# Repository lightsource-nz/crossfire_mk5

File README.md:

# crossfire

USB-MIDI forwarding between every instrument on the host port: notes played on one instrument
reach all the others, with no computer in between.

crossfire runs on its own board, the **crossfire production board, revision 0.1** -- an RP2350
hosting four instruments through an on-board hub, powered and reached over one USB-C port, with
two indicators in place of a display. That is the default target of every script here. The same
application also runs on two development boards: a Pico 2 wearing the Pico-OLED-1.3, and the
stock RP2040 Pico, both with a small OLED status display.

## The production board, revision 0.1

Revision 0.1 went to the fabricator, assembled, in October 2026, and is the board the firmware
here runs on. Its design, and every decision behind it, is in `pcb/` (`pcb/README.md`); the files
that were submitted and a specification of the board as built are in `pcb/releases/v0.1/`. The
design files themselves have since moved on to revision 0.2.

The firmware target is `crossfire_v01`: its own pico-sdk board definition in `boards/`, its wiring
in `crates/light-board-crossfire-v01`, and the application instantiated in `module/crossfire_v01`.
Its instruments are hosted on a PIO pair to the on-board hub -- the framework's `usb-host-pio`
role, the same host stack the development boards run on their native controller -- and its USB-C
port is the device: the console rides it, as well as the debug header's UART, and so does the
1200-baud route into the bootloader, so the board is written over its own connector with no probe.
The build fixes the system clock at 240 MHz (`CROSSFIRE_V01_SYS_CLK_KHZ`; 192000 and 120000 are
the alternatives), because the PIO host wants a multiple of 12 MHz and the SDK's default is not
one. What it shares with the Pico 2 below the application -- probation, firmware
self-replacement -- is `crates/crossfire-rp2350`.

With no display, it shows its state on two indicators: green lit while an instrument is mounted
and interrupted by traffic, red lit while the supply is known to be short of what four ports could
ask for. It reads that from the receptacle's CC lines twice a second, since a worn cable's CC
contact can make and break after start-up (`power` on the console reports them on request),
releases the on-board hub once the host stack is listening and the supply's advertisement has held
for 100 ms, or after a second without one (`hub on|off` re-enumerates it or holds it), and `stats`
reports the PIO host's frame engine beside the application's own counters.

What has been shown on the board: the PIO host enumerates the hub and two USB-MIDI instruments
behind it, and notes played on them reach the board and are forwarded, with the activity indicator
following. The CC lines read all three advertisements correctly -- the USB default, 1.5 A and
3 A -- and the default and 3 A on either line, as the cable is turned over. A new image reaches it
over its console and keeps itself (below). `scripts/read-cc.ps1` reads the CC lines through the
debug header, which leaves the USB-C port free for the supply under test. Running from a USB-PD
supply, a keyboard played a synth through the board, notes and chords starting and stopping as
played, with the synth's controls reaching the keyboard the other way. `trace on` on the console
logs every message read from and written to each instrument, and `send` writes one to an instrument
directly. Measured from its ports (below), a message crosses it in 0.2 to 1.3 ms and nothing is lost
up to 16,000 messages a second. Not yet shown on hardware: the recovery of a hub port disabled for a device error, which
is tested on the host only.

## Building

This project is built against the **light framework** checkout beside it (`../light_mk5`); set
`LIGHT_PATH` for another layout. The framework supplies the C shell, the portable crates, the
ports, the asset compilers and the shared script layer. Everything that is crossfire's own --
the application, the board modules, the version, the signing key, the flash map -- is here.

```
scripts/build.ps1 [-Target crossfire_v01|crossfire_pico2|crossfire_pico]
scripts/flash.ps1                             # the production board, over its own USB-C port
scripts/update.ps1                            # the production board, while it runs (below)
scripts/console.ps1                           # its console, on the same port
scripts/flash.ps1 -Target crossfire_pico2     # a Pico, over SWD through a debug probe
scripts/debug.ps1 -Target crossfire_pico2
scripts/console.ps1 -Port <COM>               # a Pico's console rides the probe's UART
scripts/test.ps1                              # the application's host tests
```

With no `-Target`, the scripts build and write `crossfire_v01`, the production board.

CI (`.github/workflows/ci.yml`) runs the same scripts through the framework's reusable workflows:
the host tests, and a firmware build of each board -- the two RP2350 legs with their bootloader --
whose images are kept as artifacts.

## Running it without a board

```
scripts/sim.ps1 [-Release]                    # crossfire on a simulated board, in a window
```

`tools/crossfire-sim` runs the application crate -- the same one the firmware links, unchanged --
over the framework's simulated seams (`light_mk5/tools/light-sim`): an SH1107 panel that decodes
the real driver's commands onto a simulated glass, the indicator, the BOOTSEL button, a hub with
four sockets that instruments plug into and play from, and the console, in a desktop window. The
font, the look-and-feel and the interface are compiled at start-up by the same code the firmware
build runs, so the glass shows what the panel shows. Console lines can also be piped in on standard
input, and the log is echoed to standard output. What it simulates is the application's logic
against its seams, with a person at the controls; it is not a model of a chip, and the host tests
remain the place a module's behaviour is pinned down. The board it stands in for is a Pico with
the Pico-OLED-1.3; the production board's two indicators are not simulated yet.

## Images are signed

Every build signs its image and the device's flash map with `keys/dev.pem`, which is public and
protects nothing (see `keys/README.md`); a release is signed with a key that never appears here.
The flash map gives the application an A/B pair, so an update is written to the slot that is not
running and chosen on the next boot, and a data partition for the assets. What the hardware
verifies, and when, is specified in the framework's `documents/11-secure-boot-and-update.md`.

## A new image keeps itself only if it works

An update is started on probation: the RP2350's boot ROM runs it once, and unless it commits itself
the previous image boots again -- at the next reset, or when the ROM's probation watchdog runs out
some seventeen seconds after the boot. crossfire makes that decision on its own
(`crates/light_app_crossfire/src/probation.rs`). At boot the board asks the ROM whether the running
image is a candidate; if so, the application watches itself for three seconds after every module has
loaded and commits once the main loop is turning over, the console core is alive, and the display
has taken a whole frame with no bus timeout. A panic, a stopped loop or a failed check means no
commit, and so the old firmware comes back; a candidate that has not passed by ten seconds of uptime
is given up on well inside the ROM's window. The console reports every step as `probation: ...`.
The production board has no display and is not asked about one. The RP2040 has no second slot and
puts nothing on probation, so there every image is already kept.

An image reaches the other slot over the console, so a board that is running needs no BOOTSEL, no
button and no probe to be given new firmware: `scripts/update.ps1` builds the production board's
image, sends it over the board's own USB-C port a line at a time (the console commands `receive`
and `rx`), and follows the board through its reboot to say whether the new image kept itself and
which slot it is running. A 161 KiB image takes about fifteen seconds. The board has to be running
firmware that has these commands, which `scripts/flash.ps1` puts on once.

## Measuring a board

Two small boards plugged into crossfire's ports measure it the way an instrument sees it
(`crates/crossfire-bench`). The **timer**, an RP2350-Zero with a debug probe on its SWD pads, sends
numbered messages through the board. The **echo**, an RP2040-Zero, sends each one back and toggles a
wire to the timer as it arrives (GP2 to GP2, with a ground wire beside it). Nothing else should be
plugged into crossfire during a run. The timer records three things:

- latency one way, from sending a message to the echo's wire changing;
- the round trip, from sending to the echo arriving back;
- throughput, at rates from 500 to 24,000 messages a second, with every gap in the echoes counted.

```
scripts/flash.ps1 -Target crossfire_bench_echo    # once, with BOOT held as it is plugged into the computer
scripts/bench.ps1 -Flash                          # writes the timer over SWD, runs, prints the figures
scripts/bench.ps1                                 # another run
```

The echo's OUT endpoint takes sixty-four bytes. Hold its GP3 to ground at power-up to give it four
bytes instead, like an instrument that takes one event at a time. The timer's figures stay in RAM,
and the script reads them over SWD without halting anything; its log is on the UART at GP0.

What the production board measures, with the sixty-four-byte echo:

| | min | median | 99th percentile | max |
|---|---|---|---|---|
| one way | 0.22 ms | 0.74 ms | 1.23 ms | 1.26 ms |
| round trip | 1.2 ms | 1.7 ms | 2.2 ms | 2.3 ms |

Each spreads evenly over one millisecond, the USB frame: a message waits in an instrument until the
board next asks it for one, and is written to the next instrument as soon as the board has read
it. Under load it forwards every message up to 16,000 a second in each direction, the most the
timer can send and some sixteen times what a MIDI cable carries, with a round trip of 2 to 2.7 ms.
What the board cannot take is counted as `departing` in `stats`, never lost unseen. The bench
found the PIO host's two largest costs: an instrument sending each frame lost every other packet,
and every forwarded message waited a frame to be written.

## The development boards

Before the production board existed, crossfire was brought up on two Picos, and both are still
built and tested:

- **`crossfire_pico2`** -- a Pico 2 wearing the Pico-OLED-1.3. The same RP2350 as the production
  board, with the same bootloader, flash map and probation, but its instruments on the native USB
  port in its host role and an OLED status display. Flashed and debugged over SWD; its console
  rides the debug probe's UART.
- **`crossfire_pico`** -- the stock RP2040 Pico, with the same display. No second slot and no
  bootloader: its image is its whole flash. Flashed over SWD as well.

Both show their state on the display rather than on two indicators, and both need a debug probe,
which the production board does not.

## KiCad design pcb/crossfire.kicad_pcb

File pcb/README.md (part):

# crossfire hardware

The production board: an RP2350 hosting four USB instruments through a hub, with one USB-C
connector that carries both its power and its link to a computer.

**Status: the files here are revision 0.2, in design.** Revision 0.1 was ordered assembled in
October 2026 and delivered in November; it is final, and the files that went to the fabricator and
a specification of the board as built are under `releases/v0.1/`. Changes from here on are
revision 0.2's: the first, a Power Delivery sink on the upstream connector and an input rail rated
for 20 V, is in the schematic and on the board, which grew 10 mm deeper for it (under *Layout*).
Unless a section says it was measured on
revision 0.1, a number below is a budget or a datasheet figure. A predecessor design exists elsewhere as a sketch of an earlier vision; it was never
manufactured or validated, so nothing here is inherited from it — individual parts are reused only
where they stand up on their own.

**This is the reduced first design.** An earlier revision of this board carried a Power Delivery
sink on a second connector, a charger and a cell, and a radio. Those are deferred, not rejected: they
made a first board that was hard to lay out and harder to bring up, and none of them is needed to
prove the thing the product is for. That revision is kept whole in the history at commit `bb66643`.
Revision 0.2 brings the first of them back, the sink, on the one connector this board already has.

## What the board has to do

- Host four USB-MIDI instruments at once, on four type-A receptacles, each supplied from a 5 V
  rail the board makes from its input.
- Keep the firmware that already exists: the USB device role and its console, and the signed A/B
  image pair with probation.
- Present itself to a computer on the upstream connector *while* hosting the instruments, so the two
  roles live on separate interfaces.
- Take all of its power from that same upstream USB-C connector, and share out whatever the source
  there offers between the four ports and its own electronics.

## Three decisions shape everything else

### 1. Two USB roles on two interfaces

The RP2350 has **one** USB controller, and the board needs two roles at once: host for the four
instruments, device for the computer on the upstream connector. The roles are kept apart on separate
interfaces — the hardware controller takes one, and a full-speed port built in PIO takes the other.
Nothing is multiplexed and nothing switches role, so a computer and the instruments are live at the
same time.

**The hardware controller faces outward as the device, and PIO hosts the hub.** The deciding
argument is recovery, and it beats the alternative on its own terms:

- **The boot ROM drives the hardware controller.** Putting that pair on the upstream connector means
  BOOTSEL and USB DFU work on the connector the product actually has. Recovery needs no debug probe,
  no case opened, nobody on the bench.
- **It makes the risky new thing the recoverable one.** The host side is what has to be rebuilt, and
  if that goes wrong the board can still be reflashed over its own port. The other way round, a rough
  device port takes the console and DFU with it and leaves only SWD.
- **Bring-up starts working rather than blocked.** The board is programmable and has a console over
  its own connector before any of the new firmware exists, so the host side can be brought up
  incrementally against a board that already talks.

What it costs, plainly: **the host role moves onto a new transport.** The existing host stack sits
behind a host-controller seam, so the stack, the hub handling and the MIDI layer above it are kept —
but the packet-level transport underneath becomes a full-speed USB host built in PIO, which does not
exist in this tree. That is the single largest piece of new firmware this board asks for, and it is
the harder of the two roles to build: it has to generate frames, schedule transactions across four
devices and a hub, and handle retries.

The device side, by contrast, is already proven on hardware — the console rides it today. The one
addition there is the computer-facing MIDI interface, which is a device class on a working stack.

**The upstream connector is unambiguous.** It sinks power and acts as a device, both, always — so
the CC lines mean one thing, there is no role to choose, and the charger-versus-computer guess that a
multiplexed design would have needed is gone. Electrically it is also the simpler end: the hardware
controller's pins carry their own impedance matching and pull-ups, so the pair needs only an ESD
array and the receptacle's two data pairs tied together, so a cable can go in either way up.

**The PIO port sets the system clock, and it sets it upward: 240 MHz.** Full-speed bit timing off PIO
wants a system clock that is an integer multiple of 12 MHz, so the state-machine divider is exact and
the bit period carries no fractional jitter. The stock 150 MHz is not such a multiple. Going *down* to
120 MHz would satisfy it at the cost of a fifth of the loop; going up to 240 MHz satisfies it and buys
the loop instead, and four things line up on that number:

- **12 MHz × 20.** Twenty system cycles per bit, and an exact divide by two if the state machine wants
  to run at 120 MHz. Either way the divider is an integer.
- **Twenty cycles a bit is a generous instruction budget** for the hardest software on the board. Ten
  would have been tight. The clock that makes the timing legal also makes the program easier to write.
- **It is already proven on this silicon.** A board in this codebase runs RP2350 at 240 MHz today,
  from the crystal through a 1440 MHz VCO and a divide by six, at stock core voltage.
- **The flash stays at its fastest legal clock.** A 133 MHz part divided by two off 240 MHz is
  120 MHz. Higher multiples are worse here, not better: 288 MHz would need a divide by three and drop
  the flash to 96 MHz.

So the constraint that looked like a tax is a 1.6× clock increase, and the forwarding loop gets
faster rather than slower. The device port is unaffected either way — its 48 MHz comes from the other
PLL.

**It is an overclock, though, and that is the part to weigh.** 240 MHz is above the datasheet's
150 MHz. It is proven on the boards in hand; it is not characterised across a production population
or a temperature range, and a product ships into both. What to establish before committing: whether
stock core voltage still holds at temperature, and what the fallback is if it does not — 192 MHz
(12 × 16) is the next multiple down that still beats stock, and 120 MHz is the floor that always
works.

The PIO port is the host end, so it carries 27 Ω series resistors on the pair and host-side
pull-downs; the 1.5 kΩ pull-up belongs to the hub, which asserts it on its own upstream port. It runs
entirely on the board, from GPIOs to the hub, and never reaches a connector or a cable — which is the
kindest possible first home for a software-timed USB port.

One consequence of hosting on-board: **no host supplies VBUS to the hub's upstream port**, so the hub
is self-powered, and its upstream-detect input is driven by the MCU. The datasheet is explicit about
this case: a *detachable* hub divides that pin down from the upstream VBUS, but a self-powered hub
with a permanently attached host takes it "from a dedicated host control output, or the 3.3 V domain
that powers the host" — so a GPIO, which costs one pin and hands the firmware the ability to hold
the hub down until it is ready and to force a re-enumeration by toggling it. Without that pin
asserted the hub never believes it is connected.

### 2. One upstream connector, a negotiated input, and a 5 V rail the board makes

Power and data arrive on **one USB-C receptacle**. Its data pair goes to the processor's hardware
controller, as above. Its CC pair goes to a **Power Delivery sink**, which asks the source for up to
9 V, and its VBUS, after the fuse, is the board's **input rail**, `VBUS`: 5 V from a source that
offers nothing more, 9 V under a contract, and rated throughout for the 20 V a source can put
there. A buck converter makes **5 V** from the input rail for the four port switches, and the 3.3 V
buck that revision 0.1 ran from VBUS now runs from that 5 V. There is still no power path to manage
and no second source to keep apart from the first.

| | receptacle | carries |
| --- | --- | --- |
| upstream | type-C, USB 2.0, 16-pin | D+/D− to the hardware controller, CC to the PD sink, ESD, VBUS as the input rail |

**Revision 0.1 took VBUS straight to the ports, and stated what that gave up. Revision 0.2 takes it
back, and states what it costs.**

- **The ports get a regulated 5 V from any source that offers more than 5 V.** On 0.1 a port saw
  whatever the cable delivered, down to about 4.2 V with every port loaded through a poor cable.
  From a source that offers only 5 V -- a computer, or a charger with no Power Delivery -- the
  buck cannot regulate up, and does not try: near dropout it holds its high-side switch on and
  passes its input through, less its 75 mΩ switch and the inductor, so a port sees what it saw on
  0.1 less about a tenth of a volt at full load. A buck-boost would regulate that case too; it was
  weighed and not taken, because a plain buck is simpler to lay out and to bring up, and the drop is
  small against what class-compliant instruments draw.
- **The power available is what the source offers at 9 V**, 18 W from the straps' 9 V and 2 A,
  where 0.1 was held to the 15 W of 5 V at 3 A. The board's worst case is about 12.5 W at the input,
  so the contract carries four ports at full current with room. How the sink chooses is under
  *Power*, because the obvious reading of its two straps is wrong.
- **A computer is still the power source as well as the host**, and most computers offer 5 V and far
  less than 3 A. That is what the third decision is about.
- **A source that misbehaves is no longer fatal.** The sink never asks for more than 9 V, but
  everything on the input rail -- the fuse, the sink, the 5 V buck and every capacitor there -- is
  rated for 20 V, and nothing that stops at 6 V is on it: the port switches sit behind the buck,
  and the protection array's VBUS pin, which is meant for USB's 5 V, takes the regulated 5 V. Revision 0.1 accepted
  that risk; 0.2 removes it.

**The capacitance the source sees at plug-in is kept to what USB allows.** A device may present no
more than 10 µF to VBUS when it is attached. On revision 0.2 only the input rail counts: the 100 nF
at the connector, the sink's 1 µF, and the 5 V buck's two 4.7 µF and 100 nF -- 10.6 µF as printed,
the figure 0.1 shipped with. They are 50 V parts in 1206, which keep nearly all of themselves at 5
to 9 V, so the margin is thinner than 0.1's and the sum is kept to that figure deliberately. The 3.3
V buck's input capacitors sit behind the 5 V buck, which is the reason that buck runs from 5 V and
not from the input rail: its datasheet asks for more than 10 µF at its input, which the input rail
cannot also carry. Each port's 22 µF sits *behind* its switch, so it is charged through a current
limit when the hub turns that port on, not by the plug going in.

### 3. The source says what it can supply, and the firmware divides it

Four ports at full USB 2.0 current is 2 A, and the board itself takes about a quarter of an amp. A
USB-C source states how much it will supply through the CC line, and the three answers it can give
are very different budgets:

| the source advertises | the board takes | left for the four ports |
| --- | --- | --- |
| 3 A | 0.25 A | 2.75 A — every port at its full 500 mA |
| 1.5 A | 0.25 A | 1.25 A — four typical instruments, or two at full current |
| USB default (0.5 A, or 0.9 A on a USB 3 port) | 0.25 A | 0.25–0.65 A — one or two instruments |
| a Power Delivery contract at 9 V, 2 A or more | — | every port at full current, with about 5 W to spare |

**So the sink reports what the source offers, and port power is policy.** On revision 0.1 the
processor read the advertisement itself: the voltage the source's pull-up made across each CC
pin's 5.1 kΩ, through 10 kΩ and 100 nF into an ADC input. On 0.2 the CC pins belong to the sink,
which presents those 5.1 kΩ terminations itself, reads the same advertisement, and holds the result
in registers on I²C at address 0x08 -- the Type-C current at 5 V when there is no contract, and the
source's offers and the contract when there is one. So the firmware reads one place for both cases,
and the series senses and the terminations are gone; GPIO 26 and 27 carry the sink's bus instead,
along the same tracks. The sink is the part the
power framework already drives, proven on hardware against a 45 W charger.

The firmware then decides which ports to power. The hub already switches each port's power on
request and reports over-current port by port, so enforcing a budget is a matter of which ports the
host stack turns on, using requests it already makes. The 1 A threshold in each port switch protects
the hardware; the policy decides what is offered. The first firmware stops short of switching: its
host stack exposes no per-port power control, so the budget it reads drives the red indicator and
the console's `power` report, and every port is offered. Enforcing it is a later firmware's work,
on the hardware as built.

**The sink's own data pins are left open, and must stay so.** It has D+ and D− for the older
charger-detection schemes, and it starts them by itself 1.5 s after attach when no contract has
been made: it drives 0.6 V onto one line and sinks 100 µA from the other. On this board the
receptacle's pair is the processor's USB connection to a computer, which is exactly the source with
no contract, so tying the sink to it would disturb enumeration on the one connection the board
cannot afterwards recover. A source without Power Delivery is read from CC alone, which is all
revision 0.1 had. Its gate drive, for an optional switch on its own supply, is left open as well:
no switch is needed when every part on the input rail is rated for what the rail can carry.

## Block structure

```mermaid
graph LR
  C[USB-C upstream] <-->|data, hardware device| MCU
  C -->|VBUS, 5 to 20 V| B5[buck 5 V]
  C -.->|CC1, CC2| PD[PD sink]
  PD -.->|I2C| MCU
  B5 -->|5 V| P[4 port switches and type-A]
  B5 --> B33[buck 3.3 V]
  B33 --> MCU[RP2350A and flash]
  B33 --> HUB[4-port hub]
  MCU <-->|data, PIO host| HUB
  HUB <-->|data| P
  HUB -.->|port power, overcurrent| P
```

*Solid lines carry power or USB data; dashed lines are control and sensing.*

## Power

### Rails

| rail | source | sized for | why |
| --- | --- | --- | --- |
| input (`VBUS`) | the upstream connector, after the fuse | 5–20 V, about 1.4 A at 9 V | whatever the sink agreed: 9 V under a contract, 5 V without one; every part on it rated for 20 V |
| 5 V | AP64350 buck from the input | 3.5 A part, 2.5 A needed | the four ports and the 3.3 V buck; regulated from any source above 5 V, passed through from a 5 V one |
| 3.3 V | fixed-output buck from 5 V | 2 A part, 0.35 A needed | a buck rather than a linear regulator saves about 80 mA of an input budget that can be as small as half an amp |
| 1.1 V (core) | the MCU's own switching regulator | — | not a board converter, but it needs board parts: an inductor on `VREG_LX` and a feedback network, which is why it is a rail and not just decoupling |

The core rail catches people out, so it is worth stating: this MCU regulates its own core with a
*switching* regulator, not a linear one. It brings out `VREG_VIN`, `VREG_LX` and `VREG_FB`, so the
schematic carries an inductor and the rail it makes feeds the `DVDD` pins. The analogue supply for
the ADC wants its own filter off 3.3 V as well, and it now has work to do: the two CC readings come
through it.

**The 3.3 V converter is a fixed-output part, so it has no divider to get wrong.** It takes an input
capacitor, a bootstrap capacitor, an inductor and its output capacitors, and its enable is tied to
its input so it starts when the 5 V rail comes up. Its input range reaches down to 3.8 V, below
anything the 5 V buck can leave it with in dropout. Every part around it is as built on revision
0.1; only its supply moved.

**The 5 V converter is the vendor's own 5 V design, value for value.** The AP64350's datasheet
works one example through, 5 V out at 3.5 A and 500 kHz, and the board takes it whole: 115 kΩ over
22.1 kΩ to the 0.8 V reference, 200 kΩ on `RT` for 500 kHz, 14 kΩ and 3.3 nF on `COMP` for a 20
kHz crossover, 100 nF bootstrap, two 22 µF at the output. The datasheet's optional 47 pF across the
upper feedback resistor is left out, as its example leaves it. Its enable is tied to its input, which
the part allows since the pin is rated for the full input. Two numbers differ from the example and
both on purpose: the input capacitance is two 4.7 µF where the example has one 10 µF, which is the
plug-in limit above, and the inductor is a 5.6 µH part where the example's is 5.5 µH, the nearest
standard value. Its dropout behaviour is what makes a buck acceptable here at all, so it is quoted:
near its output voltage "the regulator enters low-dropout mode by holding Q1 on for multiple clock
cycles", refreshing the bootstrap capacitor through the low side as it goes, so "the effective duty
cycle is approximately 100%".

**The sink's two straps are the contract the board boots on, and the obvious reading of them is
wrong.** A fixed 100 µA flows out of `VSET` and `ISET`, and a resistor to ground on each states a
voltage and a current: 6.04 kΩ is 9 V and 10.5 kΩ is 2 A. The part forms its request from the lower
of the straps and its own factory setting, then walks the source's offers **from the highest voltage
down**, taking the first whose voltage is at or below the request and whose current is at or above
it. So the voltage strap is a *ceiling*, and the current strap is a *floor* the offer has to clear --
which runs the other way from what it looks like: asking for 3 A would make a common 18 W charger
fail its 9 V line and fall through to 5 V at 3 A, 15 W, where asking for 2 A takes 9 V at 2 A, 18 W.
The modest request is the one that wins more power. On a mismatch the `_002` variant keeps walking
down the offers rather than jumping to 5 V, and every source offers 5 V, so the walk always ends in a
contract or in the plain Type-C current the source advertises. Firmware can choose an offer over I²C
afterwards; the straps are what holds before any firmware runs.

### Budget

**3.3 V rail**

| | typical | peak |
| --- | --- | --- |
| RP2350A, both cores at 240 MHz, USB active | 110 mA | 150 mA |
| QSPI flash, executing in place | 15 mA | 25 mA |
| hub | 90 mA | 120 mA |
| indicators, crystals, pull-ups | 25 mA | 40 mA |
| **total** | **240 mA** (0.79 W) | **335 mA** (1.1 W) |

At about 90% conversion that is **175 mA typical and 250 mA peak from the 5 V rail**.

**5 V rail**

| | current | power |
| --- | --- | --- |
| full USB 2.0 spec, 4 × 500 mA | 2.00 A | 10.0 W |
| four typical MIDI instruments | 0.4–1.0 A | 2–5 W |
| the 3.3 V converter's input | 0.18–0.25 A | 0.9–1.25 W |

**Upstream**

Worst case is 2.25 A at 5 V, about 11.3 W, and about 12.5 W at the input once the 5 V buck's
losses are counted. Under a 9 V contract that is about 1.4 A from the source, inside the 2 A the
straps ask for. Without a contract the buck passes the input through and the figures are 0.1's: a
3 A source covers the worst case with margin, a 1.5 A source runs four ordinary instruments, and a
default port runs the board and one or two instruments. It is the firmware's reading of the sink
that tells those cases apart.

## Parts

Stock KiCad symbols exist for everything marked with one; the rest need drawing.

| block | part | symbol | why |
| --- | --- | --- | --- |
| MCU | RP2350A, QFN-60 | `MCU_RaspberryPi:RP2350A` | 30 GPIO is enough (see below); RP2350B if a display is added |
| flash | W25Q128JVS, 16 MB | `Memory_Flash:W25Q128JVS` | the A/B image pair plus the asset partition; 2 MB would not hold it, and its 133 MHz rating covers the 120 MHz the divider lands on |
| hub | USB2514B | `Interface_USB:USB2514B_Bi` | four downstream ports, per-port power and overcurrent pins, no external EEPROM needed |
| port switch ×4 | TPS2065C | `Power_Management:TPS2065CDBV` | 1 A threshold, **active-high enable, open-drain fault** — what the hub needs at both ends. It limits by going into constant current rather than latching off, and adds reverse blocking and output discharge, both of which a port wants. Its 0.5 A sibling is the same trap as before: that is the budget itself, with nothing for inrush |
| port data ESD ×4 | 2-channel array, low capacitance | — | needed because the switch above protects power only. The TPD3S0x4 would have covered both, but it has no fault output, so it cannot tell the hub anything |
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
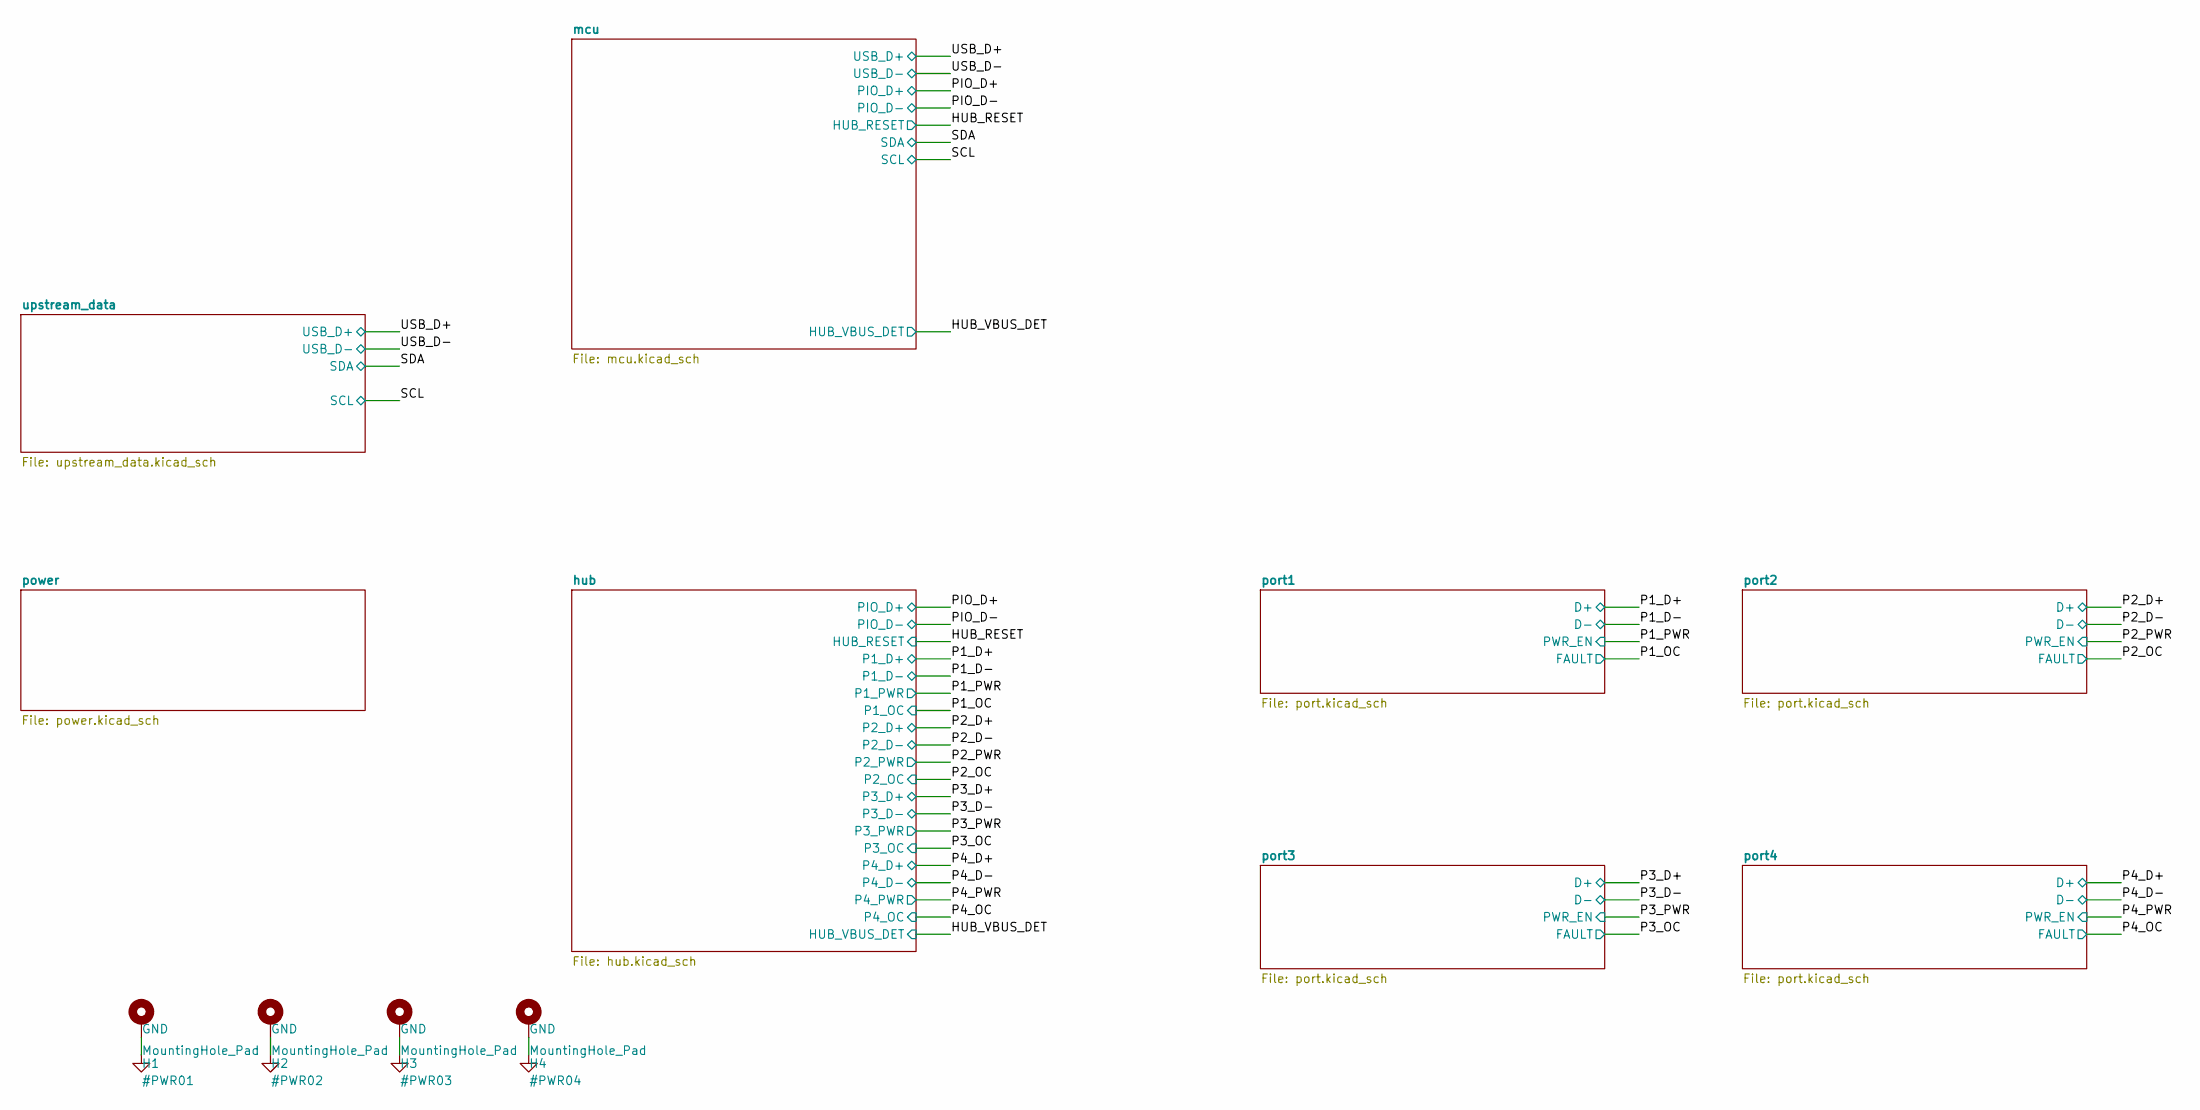
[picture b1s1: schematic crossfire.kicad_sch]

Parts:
H1, H2, H3, H4: MountingHole_Pad; MountingHole_3.2mm_M3_Pad

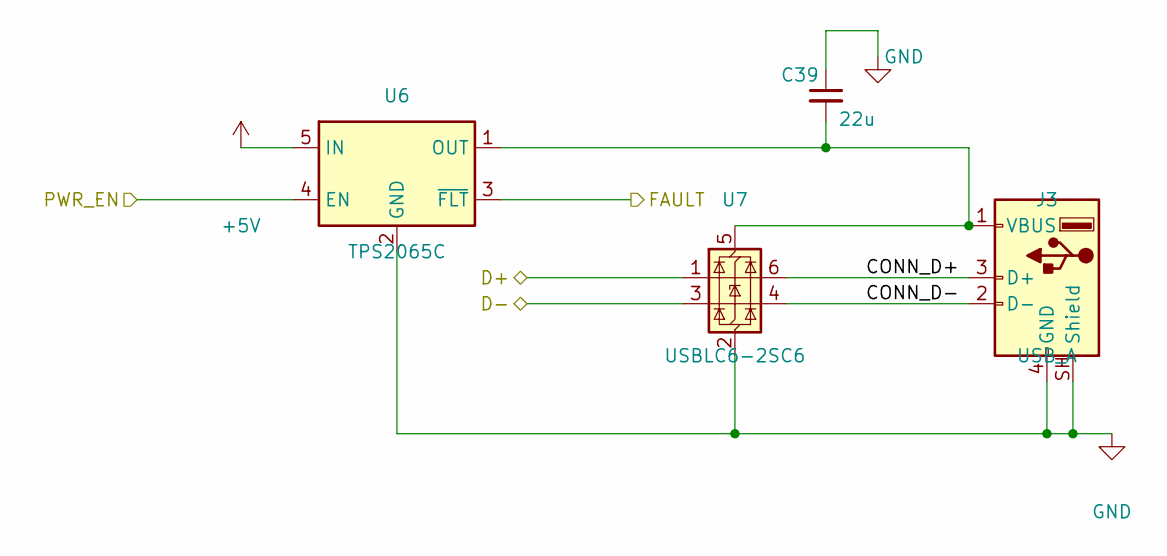
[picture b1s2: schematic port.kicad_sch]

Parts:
C39: 22u; C_1210_3225Metric; Voltage 25V
J3: USB_A; USB_A_Molex_67643_Horizontal_Overhang; MPN TE 292303-6; LCSC C591765
U6: TPS2065C; SOT-23-5; MPN TPS2065CDBVR; LCSC C353882
U7: USBLC6-2SC6; SOT-23-6; MPN USBLC6-2SC6; LCSC C7519

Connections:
/P1_D+: U7.1 (I/O1); also elsewhere on the board
/P1_D-: U7.3 (I/O2); also elsewhere on the board
/P1_OC: U6.3 (~FLT); also elsewhere on the board
/P1_PWR: U6.4 (EN); also elsewhere on the board
/port1/CONN_D+: J3.3 (D+), U7.6 (I/O1)
/port1/CONN_D-: J3.2 (D-), U7.4 (I/O2)
unnamed: C39.2, J3.1 (VBUS), U6.1 (OUT), U7.5 (VBUS)

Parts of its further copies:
C40, C41, C42: 22u; C_1210_3225Metric; Voltage 25V
J4, J5, J6: USB_A; USB_A_Molex_67643_Horizontal_Overhang; MPN TE 292303-6; LCSC C591765
U8, U10, U12: TPS2065C; SOT-23-5; MPN TPS2065CDBVR; LCSC C353882
U9, U11, U13: USBLC6-2SC6; SOT-23-6; MPN USBLC6-2SC6; LCSC C7519

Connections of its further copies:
/P2_D+: U9.1 (I/O1); also elsewhere on the board
/P2_D-: U9.3 (I/O2); also elsewhere on the board
/P2_OC: U8.3 (~FLT); also elsewhere on the board
/P2_PWR: U8.4 (EN); also elsewhere on the board
/P3_D+: U11.1 (I/O1); also elsewhere on the board
/P3_D-: U11.3 (I/O2); also elsewhere on the board
/P3_OC: U10.3 (~FLT); also elsewhere on the board
/P3_PWR: U10.4 (EN); also elsewhere on the board
/P4_D+: U13.1 (I/O1); also elsewhere on the board
/P4_D-: U13.3 (I/O2); also elsewhere on the board
/P4_OC: U12.3 (~FLT); also elsewhere on the board
/P4_PWR: U12.4 (EN); also elsewhere on the board
/port2/CONN_D+: J4.3 (D+), U9.6 (I/O1)
/port2/CONN_D-: J4.2 (D-), U9.4 (I/O2)
/port3/CONN_D+: J5.3 (D+), U11.6 (I/O1)
/port3/CONN_D-: J5.2 (D-), U11.4 (I/O2)
/port4/CONN_D+: J6.3 (D+), U13.6 (I/O1)
/port4/CONN_D-: J6.2 (D-), U13.4 (I/O2)
unnamed: C40.2, J4.1 (VBUS), U8.1 (OUT), U9.5 (VBUS)
unnamed: C41.2, J5.1 (VBUS), U10.1 (OUT), U11.5 (VBUS)
unnamed: C42.2, J6.1 (VBUS), U12.1 (OUT), U13.5 (VBUS)

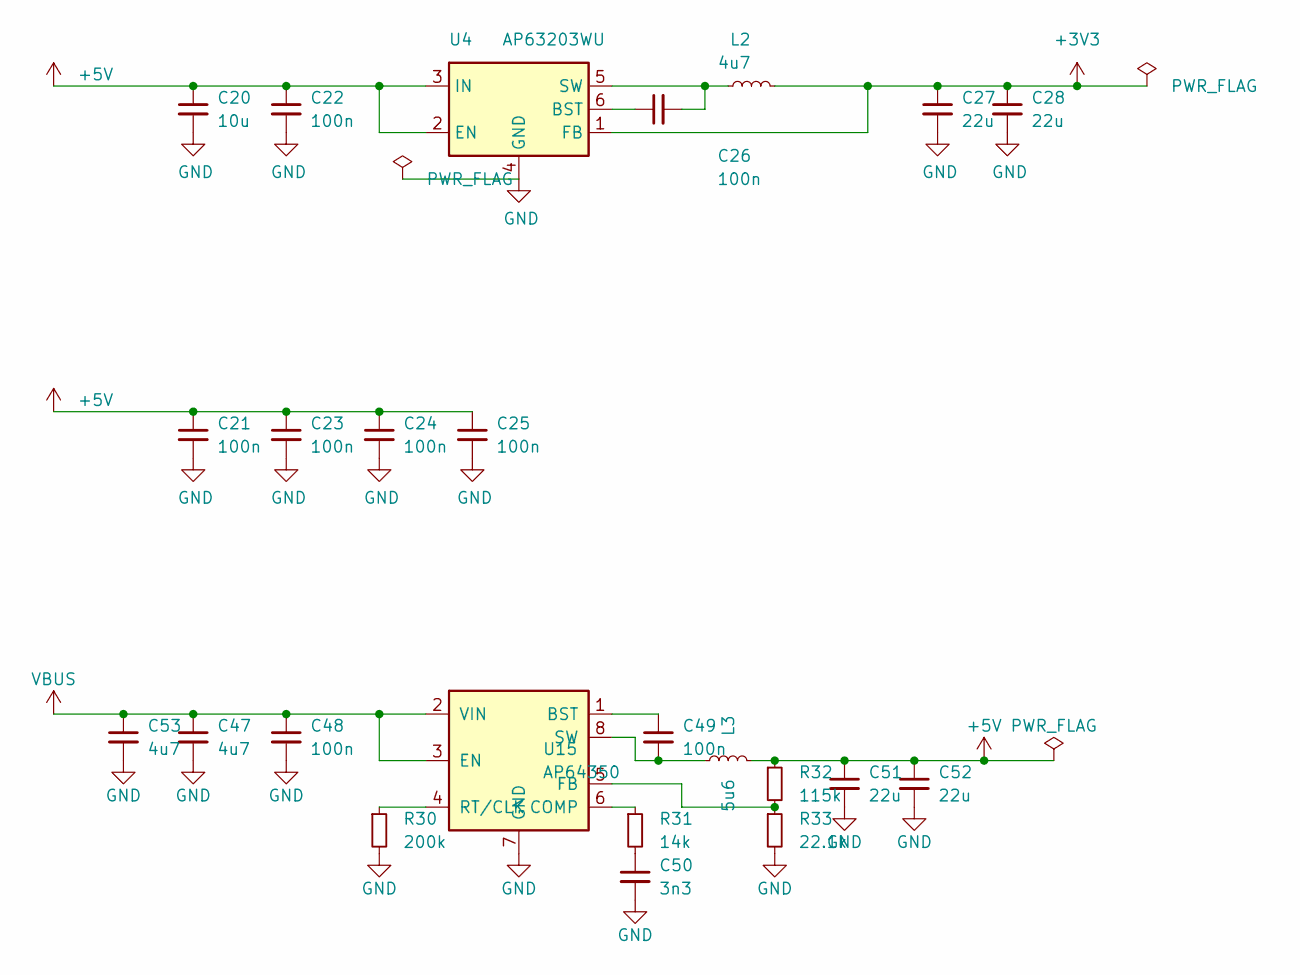
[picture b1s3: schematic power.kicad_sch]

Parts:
C20: 10u; C_0805_2012Metric; Voltage 16V; LCSC C15850
C21, C22, C23, C24, C25: 100n; C_0402_1005Metric; Voltage 25V; LCSC C1525
C26, C49: 100n; C_0402_1005Metric; Voltage 16V; LCSC C1525
C27, C28: 22u; C_0603_1608Metric; Voltage 6.3V; LCSC C59461
C47, C53: 4u7; C_1206_3216Metric; Voltage 50V; LCSC C51205
C48: 100n; C_0402_1005Metric; Voltage 50V; LCSC C307331
C50: 3n3; C_0402_1005Metric; Voltage 50V; LCSC C26404
C51, C52: 22u; C_1206_3216Metric; Voltage 25V; LCSC C12891
L2: 4u7; L_4030_Coilcraft_XxL_Sunlord_SWPA; Tolerance 20%; MPN Sunlord SWPA4030S4R7MT; LCSC C57269
L3: 5u6; L_8.8x8.2_cjiang_FXL0840; Tolerance 20%; MPN cjiang FXL0840-5R6-M; LCSC C5359252
R30: 200k; R_0402_1005Metric; Tolerance 1%; LCSC C25764
R31: 14k; R_0402_1005Metric; Tolerance 1%; LCSC C3015834
R32: 115k; R_0402_1005Metric; Tolerance 1%; LCSC C423255
R33: 22.1k; R_0402_1005Metric; Tolerance 1%; LCSC C43473
U4: AP63203WU; TSOT-23-6; MPN AP63203WU-7; LCSC C780769
U15: AP64350; SOIC-8-1EP_3.9x4.9mm_P1.27mm_EP2.41x3.3mm; MPN AP64350SP-13; LCSC C2071691

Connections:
unnamed: C50.1, R31.2
unnamed: C26.1, U4.6 (BST)
unnamed: C26.2, L2.1, U4.5 (SW)
unnamed: C49.1, U15.1 (BST)
unnamed: R31.1, U15.6 (COMP)
unnamed: R32.2, R33.1, U15.5 (FB)
unnamed: R30.1, U15.4 (RT/CLK)
unnamed: C49.2, L3.1, U15.8 (SW)
VBUS: C47.1, C48.1, C53.1, U15.2 (VIN), U15.3 (EN); also elsewhere on the board

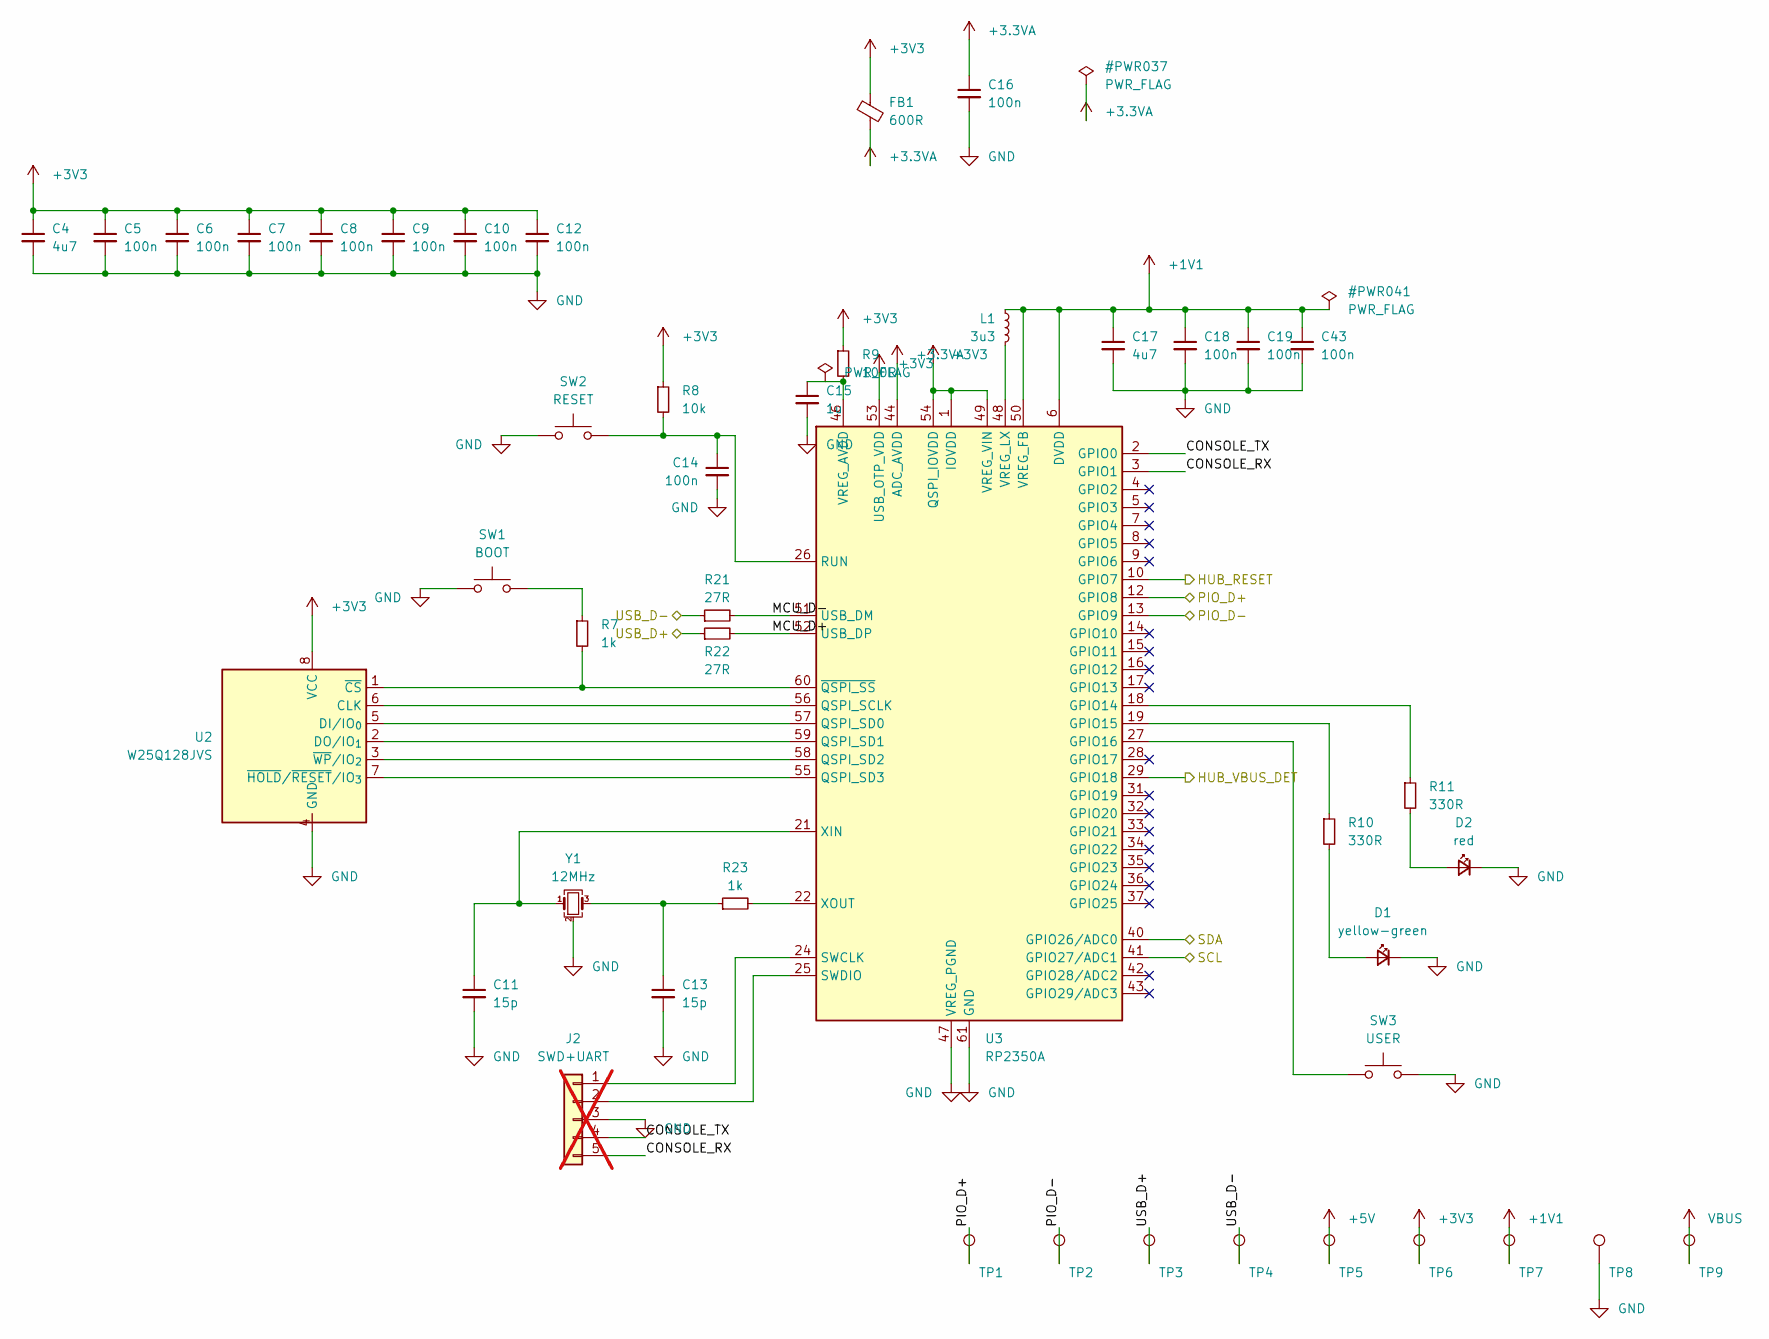
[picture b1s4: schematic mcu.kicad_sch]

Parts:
C4, C17: 4u7; C_0402_1005Metric; Voltage 10V; MPN Samsung CL05A475MP5NRNC; LCSC C23733
C5, C6, C7, C8, C9, C10, C12, C14, C16, C18, C19, C43: 100n; C_0402_1005Metric; Voltage 16V; LCSC C1525
C11, C13: 15p; C_0402_1005Metric; Voltage 50V; LCSC C1548
C15: 1u; C_0402_1005Metric; Voltage 16V; MPN Samsung CL05A105KO5NNNC; LCSC C29266
D1: yellow-green; LED_0603_1608Metric; MPN LITEON LTST-C194KGKT; LCSC C913102
D2: red; LED_0603_1608Metric; MPN KENTO KT-0603R; LCSC C2286
FB1: 600R; L_0603_1608Metric; Tolerance 25%; MPN Murata BLM18KG601SN1D; LCSC C85833
J2: SWD+UART; PinHeader_1x05_P2.54mm_Vertical; MPN 2.54 mm 1x5 header, not fitted; not fitted
L1: 3u3; abracon_aota-b201610s3r3-101-t; Tolerance 20%; MPN TDK VLS201610ET-3R3M; LCSC C114768
R7: 1k; R_0402_1005Metric; Tolerance 5%; LCSC C11702
R8: 10k; R_0402_1005Metric; Tolerance 5%; LCSC C25744
R9: 100R; R_0402_1005Metric; Tolerance 5%; LCSC C25076
R10, R11: 330R; R_0402_1005Metric; Tolerance 5%; MPN UNI-ROYAL 0402WGF3300TCE; LCSC C25104
R21, R22: 27R; R_0402_1005Metric; Tolerance 1%; MPN UNI-ROYAL 0402WGF270JTCE; LCSC C25100
R23: 1k; R_0402_1005Metric; Tolerance 1%; LCSC C11702
SW1: BOOT; SW_Push_1P1T_NO_CK_KSC6xxJ; MPN C&K KSC221JLFS; LCSC C221726
SW2: RESET; SW_Push_1P1T_NO_CK_KSC6xxJ; MPN C&K KSC221JLFS; LCSC C221726
SW3: USER; SW_Push_1P1T_NO_CK_KSC6xxJ; MPN C&K KSC221JLFS; LCSC C221726
TP1, TP2, TP3, TP4, TP5, TP6, TP7, TP8, TP9: TestPoint; TestPoint_Pad_1.0x1.0mm
U2: W25Q128JVS; SOIC-8_5.3x5.3mm_P1.27mm; MPN W25Q128JVSIQ; LCSC C97521
U3: RP2350A; rpi_rp2350a_vias; MPN RP2350A; LCSC C42411118
Y1: 12MHz; Crystal_SMD_3225-4Pin_3.2x2.5mm; Tolerance 30ppm; MPN JGHC S3212000101080; LCSC C390763

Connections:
/HUB_RESET: U3.10 (GPIO7); also elsewhere on the board
/HUB_VBUS_DET: U3.29 (GPIO18); also elsewhere on the board
/PIO_D+: TP1.1, U3.12 (GPIO8); also elsewhere on the board
/PIO_D-: TP2.1, U3.13 (GPIO9); also elsewhere on the board
/SCL: U3.41 (GPIO27/ADC1); also elsewhere on the board
/SDA: U3.40 (GPIO26/ADC0); also elsewhere on the board
/USB_D+: R22.1, TP3.1; also elsewhere on the board
/USB_D-: R21.1, TP4.1; also elsewhere on the board
/mcu/CONSOLE_RX: J2.5, U3.3 (GPIO1)
/mcu/CONSOLE_TX: J2.4, U3.2 (GPIO0)
/mcu/MCU_D+: R22.2, U3.52 (USB_DP)
/mcu/MCU_D-: R21.2, U3.51 (USB_DM)
unnamed: C13.1, R23.1, Y1.3
unnamed: D1.2 (A), R10.2
unnamed: D2.2 (A), R11.2
unnamed: J2.1, U3.24 (SWCLK)
unnamed: J2.2, U3.25 (SWDIO)
unnamed: R7.1, SW1.2
unnamed: U2.6 (CLK), U3.56 (QSPI_SCLK)
unnamed: U2.5 (DI/IO_{0}), U3.57 (QSPI_SD0)
unnamed: U2.2 (DO/IO_{1}), U3.59 (QSPI_SD1)
unnamed: R7.2, U2.1 (~CS), U3.60 (~QSPI_SS)
unnamed: U2.7 (~HOLD/~RESET/IO_{3}), U3.55 (QSPI_SD3)
unnamed: U2.3 (~WP/IO_{2}), U3.58 (QSPI_SD2)
unnamed: R11.1, U3.18 (GPIO14)
unnamed: R10.1, U3.19 (GPIO15)
unnamed: SW3.1, U3.27 (GPIO16)
unnamed: C14.1, R8.2, SW2.2, U3.26 (RUN)
unnamed: L1.2, U3.48 (VREG_LX)
unnamed: C11.1, U3.21 (XIN), Y1.1
unnamed: R23.2, U3.22 (XOUT)
VBUS: TP9.1; also elsewhere on the board

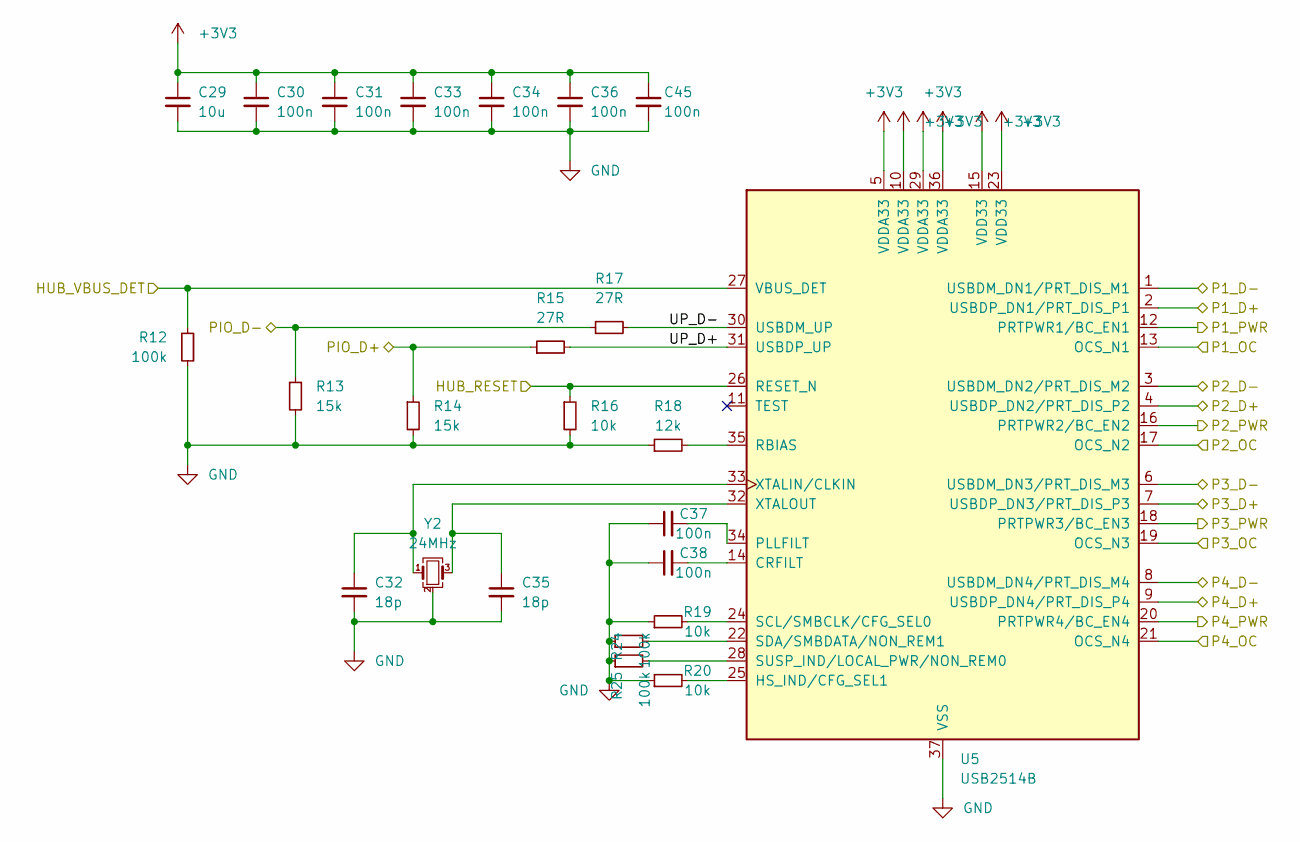
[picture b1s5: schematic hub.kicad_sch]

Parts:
C29: 10u; C_0805_2012Metric; Voltage 16V; LCSC C15850
C30, C31, C33, C34, C36, C37, C38, C45: 100n; C_0402_1005Metric; Voltage 16V; LCSC C1525
C32, C35: 18p; C_0603_1608Metric; Voltage 50V; LCSC C1647
R12, R24, R25: 100k; R_0402_1005Metric; Tolerance 5%; LCSC C25741
R13, R14: 15k; R_0402_1005Metric; Tolerance 5%; LCSC C25756
R15, R17: 27R; R_0402_1005Metric; Tolerance 1%; MPN UNI-ROYAL 0402WGF270JTCE; LCSC C25100
R16, R19, R20: 10k; R_0402_1005Metric; Tolerance 5%; LCSC C25744
R18: 12k; R_0402_1005Metric; Tolerance 1%; LCSC C25752
U5: USB2514B; QFN-36-1EP_6x6mm_P0.5mm_EP3.7x3.7mm; MPN USB2514B-AEZC-TR; LCSC C16251
Y2: 24MHz; Crystal_SMD_3225-4Pin_3.2x2.5mm; Tolerance 50ppm; MPN YXC X322524MMB4SI; LCSC C70583

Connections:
/HUB_RESET: R16.1, U5.26 (RESET_N); also elsewhere on the board
/HUB_VBUS_DET: R12.1, U5.27 (VBUS_DET); also elsewhere on the board
/P1_D+: U5.2 (USBDP_DN1/PRT_DIS_P1); also elsewhere on the board
/P1_D-: U5.1 (USBDM_DN1/PRT_DIS_M1); also elsewhere on the board
/P1_OC: U5.13 (OCS_N1); also elsewhere on the board
/P1_PWR: U5.12 (PRTPWR1/BC_EN1); also elsewhere on the board
/P2_D+: U5.4 (USBDP_DN2/PRT_DIS_P2); also elsewhere on the board
/P2_D-: U5.3 (USBDM_DN2/PRT_DIS_M2); also elsewhere on the board
/P2_OC: U5.17 (OCS_N2); also elsewhere on the board
/P2_PWR: U5.16 (PRTPWR2/BC_EN2); also elsewhere on the board
/P3_D+: U5.7 (USBDP_DN3/PRT_DIS_P3); also elsewhere on the board
/P3_D-: U5.6 (USBDM_DN3/PRT_DIS_M3); also elsewhere on the board
/P3_OC: U5.19 (OCS_N3); also elsewhere on the board
/P3_PWR: U5.18 (PRTPWR3/BC_EN3); also elsewhere on the board
/P4_D+: U5.9 (USBDP_DN4/PRT_DIS_P4); also elsewhere on the board
/P4_D-: U5.8 (USBDM_DN4/PRT_DIS_M4); also elsewhere on the board
/P4_OC: U5.21 (OCS_N4); also elsewhere on the board
/P4_PWR: U5.20 (PRTPWR4/BC_EN4); also elsewhere on the board
/PIO_D+: R14.1, R15.1; also elsewhere on the board
/PIO_D-: R13.1, R17.1; also elsewhere on the board
/hub/UP_D+: R15.2, U5.31 (USBDP_UP)
/hub/UP_D-: R17.2, U5.30 (USBDM_UP)
unnamed: C38.2, U5.14 (CRFILT)
unnamed: R20.2, U5.25 (HS_IND/CFG_SEL1)
unnamed: C37.2, U5.34 (PLLFILT)
unnamed: R18.2, U5.35 (RBIAS)
unnamed: R19.2, U5.24 (SCL/SMBCLK/CFG_SEL0)
unnamed: R24.2, U5.22 (SDA/SMBDATA/NON_REM1)
unnamed: R25.2, U5.28 (SUSP_IND/LOCAL_PWR/NON_REM0)
unnamed: C32.1, U5.33 (XTALIN/CLKIN), Y2.1
unnamed: C35.1, U5.32 (XTALOUT), Y2.3

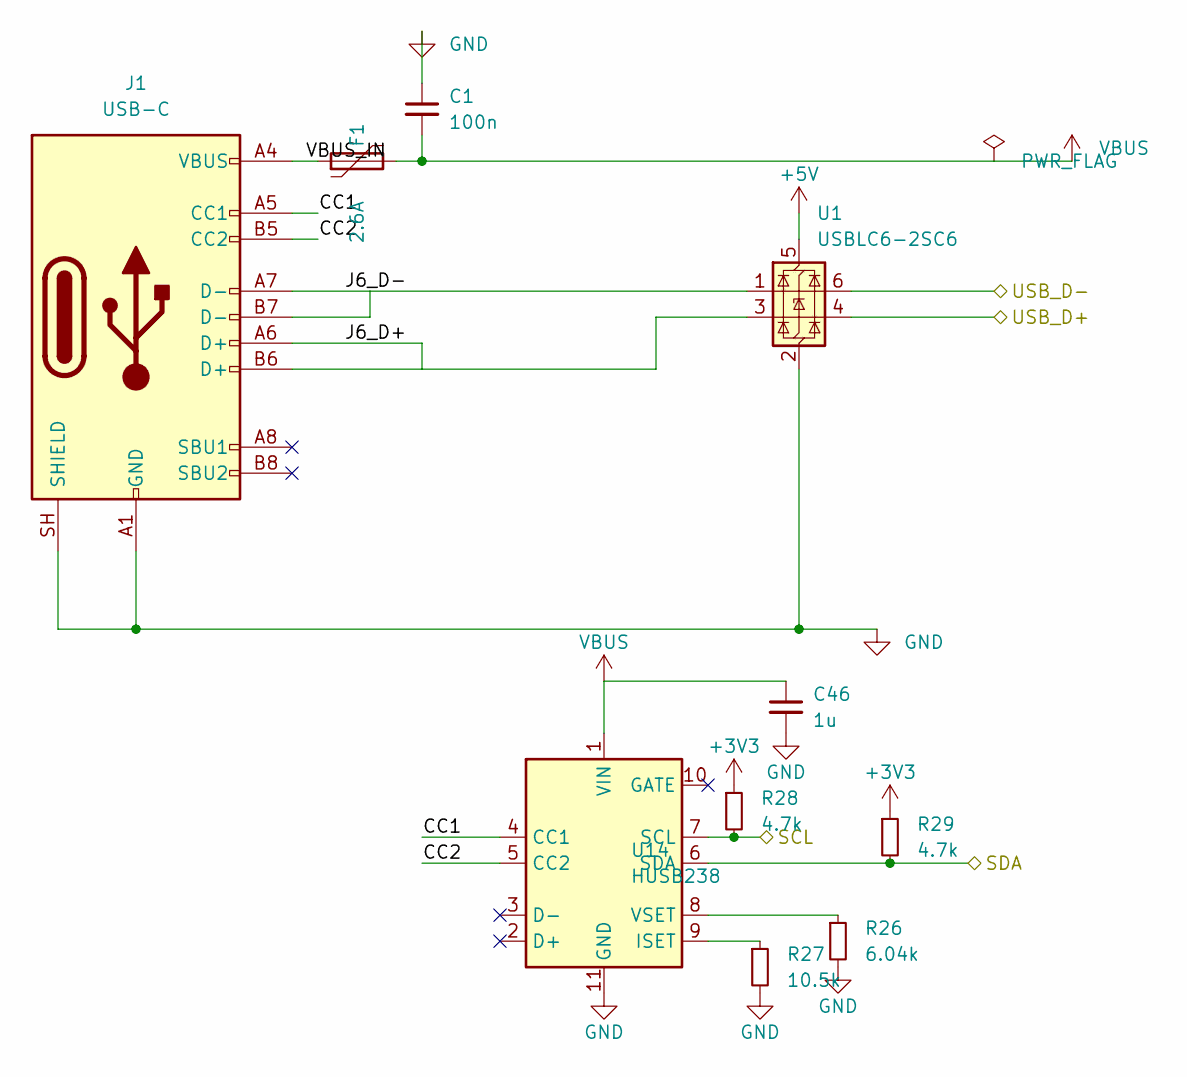
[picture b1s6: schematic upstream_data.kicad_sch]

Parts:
C1: 100n; C_0402_1005Metric; Voltage 50V; LCSC C307331
C46: 1u; C_0603_1608Metric; Voltage 50V; LCSC C5199872
F1: 2.6A; Fuse_1812_4532Metric; Voltage 24V; MPN TECHFUSE mSMD260-24V; LCSC C6851471
J1: USB-C; USB_C_Receptacle_HRO_TYPE-C-31-M-12_Overhang; MPN Korean Hroparts TYPE-C-31-M-12; LCSC C165948
R26: 6.04k; R_0402_1005Metric; Tolerance 1%; LCSC C25913
R27: 10.5k; R_0402_1005Metric; Tolerance 1%; LCSC C25850
R28, R29: 4.7k; R_0402_1005Metric; Tolerance 5%; LCSC C25900
U1: USBLC6-2SC6; SOT-23-6; MPN USBLC6-2SC6; LCSC C7519
U14: HUSB238; DFN-10-1EP_3x3mm_P0.5mm_EP1.65x2.38mm; MPN HUSB238_002DD; LCSC C7471904

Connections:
/SCL: R28.2, U14.7 (SCL); also elsewhere on the board
/SDA: R29.2, U14.6 (SDA); also elsewhere on the board
/USB_D+: U1.4 (I/O2); also elsewhere on the board
/USB_D-: U1.6 (I/O1); also elsewhere on the board
/upstream_data/CC1: J1.A5 (CC1), U14.4 (CC1)
/upstream_data/CC2: J1.B5 (CC2), U14.5 (CC2)
/upstream_data/J6_D+: J1.A6 (D+), J1.B6 (D+), U1.3 (I/O2)
/upstream_data/J6_D-: J1.A7 (D-), J1.B7 (D-), U1.1 (I/O1)
/upstream_data/VBUS_IN: F1.1, J1.A4 (VBUS), J1.A9 (VBUS), J1.B4 (VBUS), J1.B9 (VBUS)
unnamed: R27.1, U14.9 (ISET)
unnamed: R26.1, U14.8 (VSET)
VBUS: C1.2, C46.1, F1.2, U14.1 (VIN); also elsewhere on the board

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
